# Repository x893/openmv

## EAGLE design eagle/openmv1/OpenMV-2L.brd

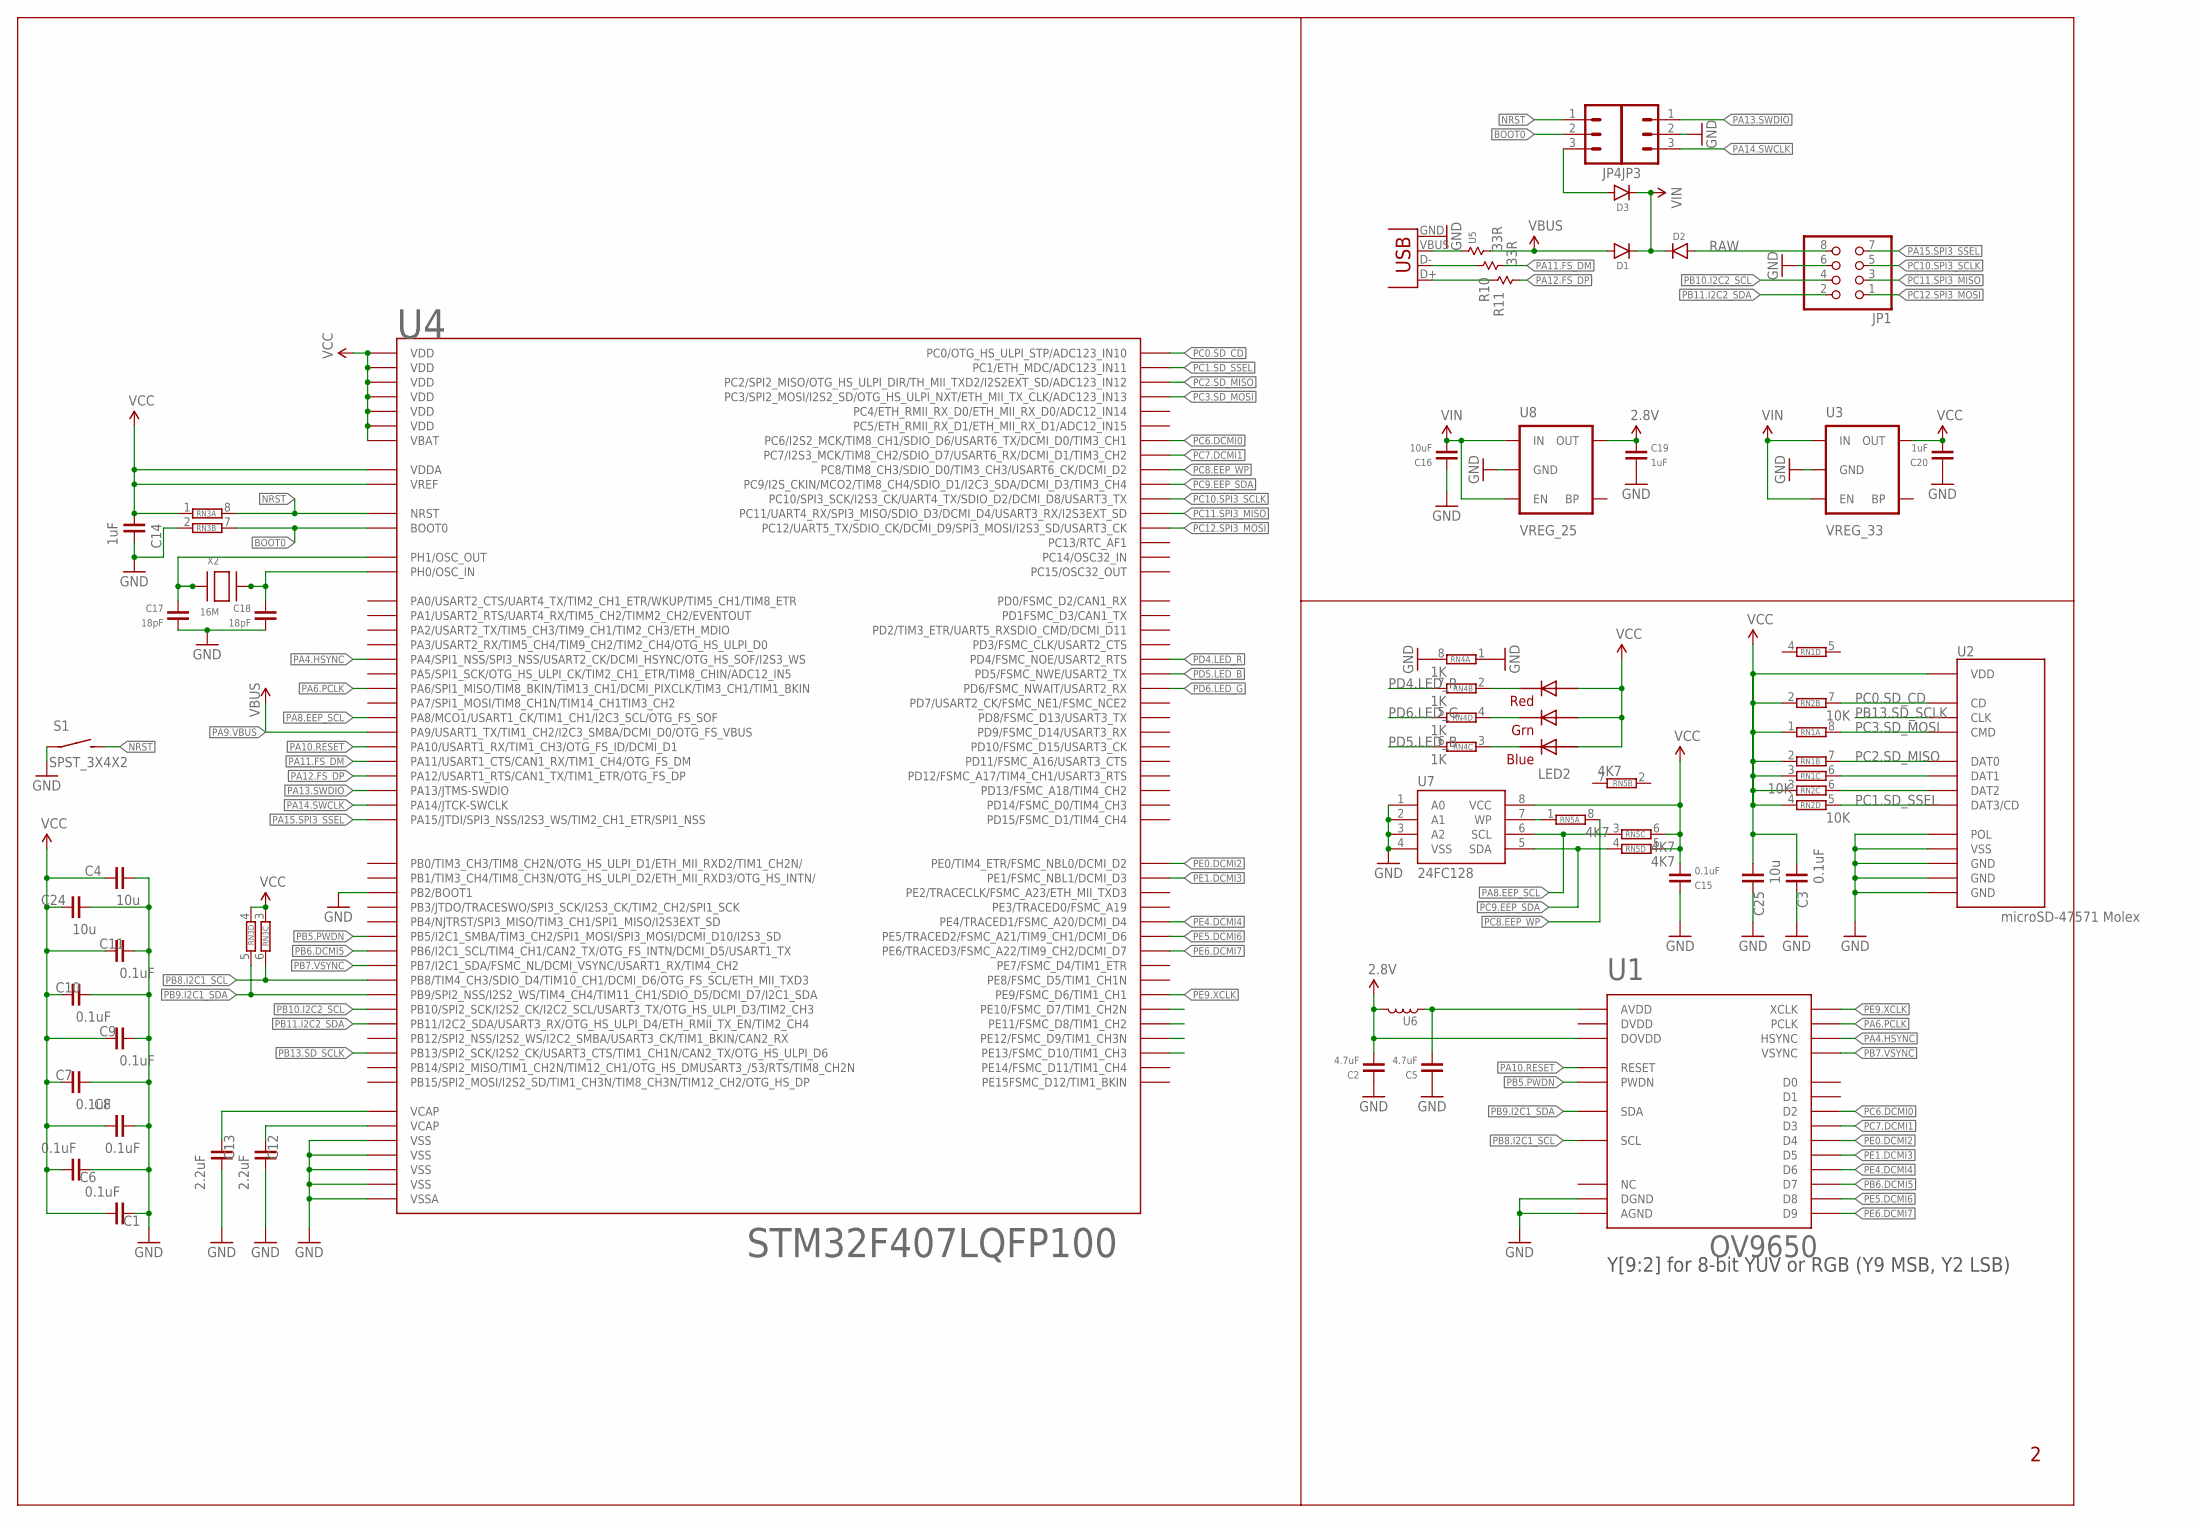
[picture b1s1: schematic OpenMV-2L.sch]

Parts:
C1, C3, C6, C7, C8, C9, C10, C11: 0.1uF; 0402
C2, C5: 4.7uF; 0603
C4, C24, C25: 10u; 0805
C12, C13: 2.2uF; 0402
C14: 1uF; 0402
C15: 0.1uF; 0603
C16: 10uF; 0805
C17, C18: 18pF; 0402
C19, C20: 1uF; 0603
D1, D2, D3: DIODE-SOD-323; SOD-323
JP1: PINHD-2X4; 2X04
JP3, JP4: M03PTH; 1X03
LED2: RGBLED5050
R10, R11: 33R; 0402
RN1, RN3: 4R-NCAT16; CAT16
RN2: 10K; CAT16
RN4: 1K; CAT16
RN5: 4K7; CAT16
S1: SPST_3X4X2; 3X4X2TACT
U1: OV9650
U2: microSD-47571 Molex; USD-47571
U3: VREG_33; SOT23-5
U4: STM32F407LQFP100; LQFP100
U5: RESISTOR-0402; 0402
U6: INDUCTOR-0603; 0603
U7: 24FC128; MSOP8
U8: VREG_25; SOT23-5
X1: USB-MICROB
X2: 16M; NX5032

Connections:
2.8V: C2.1, C19.2, U1.P$11 (DOVDD), U6.2, U8.5 (OUT)
BOOT0: JP4.2, RN3.7 (2), U4.94 (BOOT0)
GND: C1.1, C2.2, C3.2, C4.1, C5.2, C6.1, C7.2, C8.1, C9.2, C10.2, C11.2, C12.2, C13.2, C14.1, C15.2, C16.2, C17.1, C18.1, C19.1, C20.2, C24.1, C25.2, JP1.6, JP3.2, RN3.2 (1), RN4.1, RN4.8 (2), S1.P$1, U1.P$2 (AGND), U1.P$15 (DGND), U2.G$1 (GND), U2.G$2 (GND), U2.G$3 (GND), U2.G$4 (POL), U2.P$6 (VSS), U3.2 (GND), U4.10 (VSS), U4.20 (VSSA), U4.27 (VSS), U4.37 (PB2/BOOT1), U4.74 (VSS), U4.99 (VSS), U7.1 (A0), U7.2 (A1), U7.3 (A2), U7.4 (VSS), U8.2 (GND), X1.GND
unnamed: RN1.6 (2), U2.P$8 (DAT1)
unnamed: RN2.6 (2), U2.P$1 (DAT2)
unnamed: LED2.5 (RED_C), RN4.2 (1)
unnamed: LED2.6 (GREEN_C), RN4.4 (1)
unnamed: LED2.4 (BLUE_C), RN4.3 (1)
unnamed: C17.2, U4.13 (PH1/OSC_OUT), X2.P$1
unnamed: C18.2, U4.12 (PH0/OSC_IN), X2.P$2
unnamed: RN5.1, U7.7 (WP)
unnamed: C5.1, U1.P$4 (AVDD), U6.1
unnamed: D3.2 (A), JP4.3
unnamed: R10.1, X1.D-
unnamed: R11.1, X1.D+
unnamed: U5.1, X1.VBUS
NRST: JP4.1, RN3.8 (2), S1.P$2 (S), U4.14 (NRST)
PA4.HSYNC: U1.P$9 (HSYNC), U4.29 (PA4/SPI1_NSS/SPI3_NSS/USART2_CK/DCMI_HS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)
PA6.PCLK: U1.P$17 (PCLK), U4.31 (PA6/SPI1_MISO/TIM8_BKIN/TIM13_CH1/DCMI_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)
PA8.EEP_SCL: RN5.3 (1), U4.67 (PA8/MCO1/USART1_CK/TIM1_CH1/I2C3_SCL/OT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), U7.6 (SCL)
PA9.VBUS: D1.2 (A), U4.68 (PA9/USART1_TX/TIM1_CH2/I2C3_SMBA/DCMI_D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), U5.2
PA10.RESET: U1.P$6 (RESET), U4.69 (PA10/USART1_RX/TIM1_CH3/OTG_FS_ID/DCMI_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)
PA11.FS_DM: R10.2, U4.70 (PA11/USART1_CTS/CAN1_RX/TIM1_CH4/OTG_FS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)
PA12.FS_DP: R11.2, U4.71 (PA12/USART1_RTS/CAN1_TX/TIM1_ETR/OTG_FS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)
PA13.SWDIO: JP3.1, U4.72 (PA13/JTMS-SWDIO)
PA14.SWCLK: JP3.3, U4.76 (PA14/JTCK-SWCLK)
PA15.SPI3_SSEL: JP1.7, U4.77 (PA15/JTDI/SPI3_NSS/I2S3_WS/TIM2_CH1_ETR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)
PB5.PWDN: U1.P$8 (PWDN), U4.91 (PB5/I2C1_SMBA/TIM3_CH2/SPI1_MOSI/SPI3_M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)
PB6.DCMI5: U1.P$16 (D7), U4.92 (PB6/I2C1_SCL/TIM4_CH1/CAN2_TX/OTG_FS_IN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)
PB7.VSYNC: U1.P$7 (VSYNC), U4.93 (PB7/I2C1_SDA/FSMC_NL/DCMI_VSYNC/USART1_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)
PB8.I2C1_SCL: RN3.6 (2), U1.P$5 (SCL), U4.95 (PB8/TIM4_CH3/SDIO_D4/TIM10_CH1/DCMI_D6/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)
PB9.I2C1_SDA: RN3.5 (2), U1.P$3 (SDA), U4.96 (PB9/SPI2_NSS/I2S2_WS/TIM4_CH4/TIM11_CH1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)
PB10.I2C2_SCL: JP1.4, U4.47 (PB10/SPI2_SCK/I2S2_CK/I2C2_SCL/USART3_T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)
PB11.I2C2_SDA: JP1.2, U4.48 (PB11/I2C2_SDA/USART3_RX/OTG_HS_ULPI_D4/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)
PB13.SD_SCLK: U2.P$5 (CLK), U4.52 (PB13/SPI2_SCK/I2S2_CK/USART3_CTS/TIM1_C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)
PC0.SD_CD: RN2.7 (2), U2.G$5 (CD), U4.15 (PC0/OTG_HS_ULPI_STP/ADC123_IN10)
PC1.SD_SSEL: RN2.5 (2), U2.P$2 (DAT3/CD), U4.16 (PC1/ETH_MDC/ADC123_IN11)
PC2.SD_MISO: RN1.7 (2), U2.P$7 (DAT0), U4.17 (PC2/SPI2_MISO/OTG_HS_ULPI_DIR/TH_MII_TX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)
PC3.SD_MOSI: RN1.8 (2), U2.P$3 (CMD), U4.18 (PC3/SPI2_MOSI/I2S2_SD/OTG_HS_ULPI_NXT/E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)
PC6.DCMI0: U1.P$19 (D2), U4.63 (PC6/I2S2_MCK/TIM8_CH1/SDIO_D6/USART6_TX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)
PC7.DCMI1: U1.P$21 (D3), U4.64 (PC7/I2S3_MCK/TIM8_CH2/SDIO_D7/USART6_RX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)
PC8.EEP_WP: RN5.8 (2), U4.65 (PC8/TIM8_CH3/SDIO_D0/TIM3_CH3/USART6_CK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)
PC9.EEP_SDA: RN5.4 (1), U4.66 (PC9/I2S_CKIN/MCO2/TIM8_CH4/SDIO_D1/I2C3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), U7.5 (SDA)
PC10.SPI3_SCLK: JP1.5, U4.78 (PC10/SPI3_SCK/I2S3_CK/UART4_TX/SDIO_D2/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)
PC11.SPI3_MISO: JP1.3, U4.79 (PC11/UART4_RX/SPI3_MISO/SDIO_D3/DCMI_D4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)
PC12.SPI3_MOSI: JP1.1, U4.80 (PC12/UART5_TX/SDIO_CK/DCMI_D9/SPI3_MOSI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)
PD4.LED_R: RN4.7 (2), U4.85 (PD4/FSMC_NOE/USART2_RTS)
PD5.LED_B: RN4.6 (2), U4.86 (PD5/FSMC_NWE/USART2_TX)
PD6.LED_G: RN4.5 (2), U4.87 (PD6/FSMC_NWAIT/USART2_RX)
PE0.DCMI2: U1.P$22 (D4), U4.97 (PE0/TIM4_ETR/FSMC_NBL0/DCMI_D2)
PE1.DCMI3: U1.P$20 (D5), U4.98 (PE1/FSMC_NBL1/DCMI_D3)
PE4.DCMI4: U1.P$18 (D6), U4.3 (PE4/TRACED1/FSMC_A20/DCMI_D4)
PE5.DCMI6: U1.P$14 (D8), U4.4 (PE5/TRACED2/FSMC_A21/TIM9_CH1/DCMI_D6)
PE6.DCMI7: U1.P$12 (D9), U4.5 (PE6/TRACED3/FSMC_A22/TIM9_CH2/DCMI_D7)
PE9.XCLK: U1.P$13 (XCLK), U4.40 (PE9/FSMC_D6/TIM1_CH1)
RAW: D2.2 (A), JP1.8
VCAP1: C13.1, U4.49 (VCAP)
VCAP2: C12.1, U4.73 (VCAP)
VCC: C1.2, C3.1, C4.2, C6.2, C7.1, C8.2, C9.1, C10.1, C11.1, C14.2, C15.1, C20.1, C24.2, C25.1, LED2.1 (GREEN_A), LED2.2 (RED_A), LED2.3 (BLUE_A), RN1.1, RN1.2 (1), RN1.3 (1), RN2.2 (1), RN2.3 (1), RN2.4 (1), RN3.1, RN3.3 (1), RN3.4 (1), RN5.5 (2), RN5.6 (2), U2.P$4 (VDD), U3.5 (OUT), U4.6 (VBAT), U4.11 (VDD), U4.19 (VDD), U4.21 (VREF), U4.22 (VDDA), U4.28 (VDD), U4.50 (VDD), U4.75 (VDD), U4.100 (VDD), U7.8 (VCC)
VIN: C16.1, D1.1 (C), D2.1 (C), D3.1 (C), U3.1 (IN), U3.3 (EN), U8.1 (IN), U8.3 (EN)

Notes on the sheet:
Y[9:2] for 8-bit YUV or RGB (Y9 MSB, Y2 LSB)

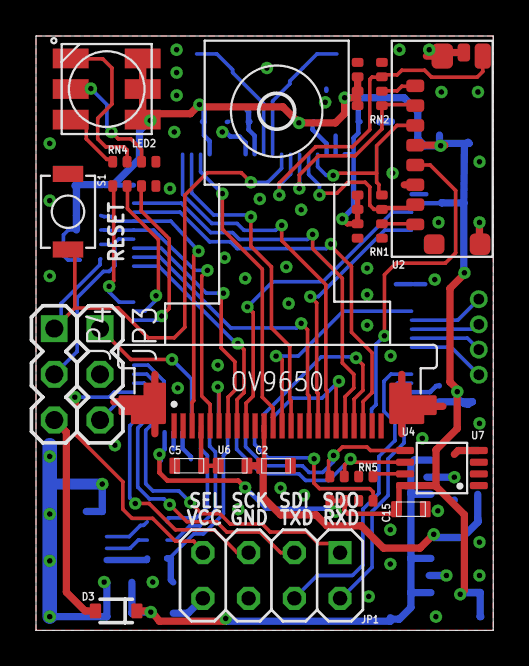
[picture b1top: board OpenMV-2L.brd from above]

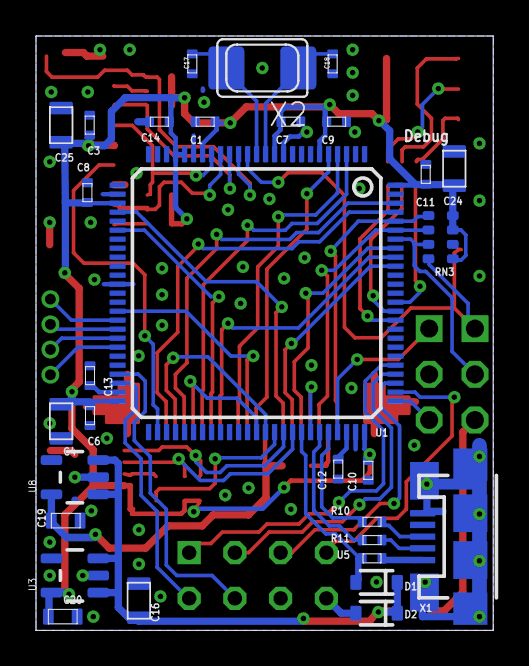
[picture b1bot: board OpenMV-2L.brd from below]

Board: 2 copper layers, 25.4 x 33.0 mm, 47 parts (30 on the bottom side), 60 nets.

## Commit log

2016-07-31 Change microphyton link
2016-07-31 Change for OpenMV1
2016-07-31 Change OpenMN1 with STM32F407VG
2016-07-31 Remove WINC1500 support
2016-08-01 Change bootloader for OpenMV1
